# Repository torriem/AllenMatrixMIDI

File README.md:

# Allen MOS II Organ Keyboard Matrix to USB MIDI Adapter
This is a Teensy 4.1 sketch for connecting an Allen MOS II Organ's keyboards to a computer over USB MIDI.  It's designed to read the 11x18 combined keyboard matrix, and export them as a MIDI device suitable to connect to any virtual pipe organ.

## Operation
The keyboards all share a common set of read wires.  Each keyboard uses 11 read wires and the pedal board uses 7 of the 11.  Each keyboard has its own set of six signal wires.  To read the keyboards a microcontroller (the organ itself or a Teensy) raises each signal wire in turn to a high state and then reads the key pressed signals from the read wires.  This is done in a sequential cycle, reading many times per second. In this way a relatively few wires can read the entire keyboard quickly, and multiple keys can be pressed at once.

The MOS II Organ, at least our vintage, has its keyboard matrices wired in a peculiar way.  The first key has it's own output wire, and subsequent groups of six keys have their own output wire.  Diodes prevent back feeding. 

The input wires are done differently. There are six input wires per keyboard and each wire feeds the input of every sixth key, with the 61st key having input wire 1 into it.

This asymmetry between the input wires and the output wire groups means the mapping is a little strange.  See the end of this document for a chart.  You can also see the mapping in the ino file.

Here's a diagram of how an individual keyboard is wired.  Both keyboards are wired like this, but each has its own set of six input wires. The pedal board also has six input wires, but only uses seven output wires.  The OUT wires in the diagram are the eleven black wires going to the keyboard matrix board edge connector.

You cannot connect the Teensy to the keyboard at the same time the normal organ circuitry is connected.  A circuit board is needed to use relays to galvanically switch the keyboard between the stock organ and the Allen internal circuitry.

The sketch turns keyboard presses and releases into MIDI NOTE ON and NOTE OFF events, with a velocity of 127.  The first keyboard events are on channel 1, the second on channel 2, and the pedal board on channel 3.  If you want to change it, you can set it in the sketch.

## Black common wires
The 11 black read wires connect to Teensy pins 20-30.  Looking at the keyboard from the top, the left-most key is connected to its own black wire to pin 20.  Every group of 6 keys after that connects via diodes to a common black wire and those go in order to pins 21 and higher.

Looking at the 44-pin MOS Matrix board connector, the connections are:

| Teensy | MOS Matrix pin |
| ------ | -------------- |
| 20     | 11             |
| 21     | 13             |
| 22     | 9              |
| 23     | 5              |
| 24     | 7              |
| 25     | 3              |
| 26     | 1              |
| 27     | 8              |
| 28     | 10             |
| 29     | 12             |
| 30     | 14             |

## Keyboard 1 Read Wires
The top keyboard matrix is read by sending high signals down six wires, each wire connected to 11 keys.  These are connected left to right to Teensy to pins 2,3,4,5,6,7.  These wires can also be accessed via the 44-pin keyboard matrix edge connector on 22,23,26,25,24, and 21. On our organ these wires are white.

| Teensy | MOS Matrix pin |
| ------ | -------------- |
| 2      | 22             |
| 3      | 23             |
| 4      | 26             |
| 5      | 25             |
| 6      | 24             |
| 7      | 21             |

## Keyboard 2 Read Wires
The second keyboard matrix is also read by sending high signals through six wires that connect to Teensy's pins 8,9,10,11,12,and 13.  On our organ these are orange wires and are connected to the edge connector to pins 28, 29, 32, 31, 30, and 27.

| Teensy | MOS Matrix pin |
| ------ | -------------- |
| 8      | 28             |
| 9      | 29             |
| 10     | 32             |
| 11     | 31             |
| 12     | 30             |
| 13     | 27             |

## Pedal Board Read Wires
The pedal board is read by sending high signals to six wires that connect to Teensy pins 14, 15, 16, 17, 18, and 19.  These wires are blue on our organ and connect to pins 40, 41, 44, 43, 42, and 39 on the 44 pin matrix edge connector. Note that only the first seven of the black read wires are used on the pedal board

| Teensy | MOS Matrix pin |
| ------ | -------------- |
| 14     | 40             |
| 15     | 41             |
| 16     | 44             |
| 17     | 43             |
| 18     | 42             |
| 19     | 39             |

## Mapping of keyboard wires to key/note

| Key | Note | Input | Output | Combination |
|-----|------|-------|--------|-------------|
|  1  | C2   | IN1   | OUT1    | IN1-OUT1 |
|  2  | C#2  | IN2   | OUT2    | IN2-OUT2 |
|  3  | D2   | IN3   | OUT2    | IN3-OUT2 |
|  4  | D#2  | IN4   | OUT2    | IN4-OUT2 |
|  5  | E2   | IN5   | OUT2    | IN5-OUT2 |
|  6  | F2   | IN6   | OUT2    | IN6-OUT2 |
|  7  | F#2  | IN1   | OUT2    | IN1-OUT2 |
|  8  | G2   | IN2   | OUT3    | IN2-OUT3 |
|  9  | G#2  | IN3   | OUT3    | IN3-OUT3 |
| 10  | A2   | IN4   | OUT3    | IN4-OUT3 |
| 11  | A#2  | IN5   | OUT3    | IN5-OUT3 |
| 12  | B2   | IN6   | OUT3    | IN6-OUT3 |
| 13  | C3   | IN1   | OUT3    | IN1-OUT3 |
| 14  | C#3  | IN2   | OUT4    | IN2-OUT4 |
| 15  | D3   | IN3   | OUT4    | IN3-OUT4 |
| 16  | D#3  | IN4   | OUT4    | IN4-OUT4 |
| 17  | E3   | IN5   | OUT4    | IN5-OUT4 |
| 18  | F3   | IN6   | OUT4    | IN6-OUT4 |
| 19  | F#3  | IN1   | OUT4    | IN1-OUT4 |
| 20  | G3   | IN2   | OUT5    | IN2-OUT5 |
| 21  | G#3  | IN3   | OUT5    | IN3-OUT5 |
| 22  | A3   | IN4   | OUT5    | IN4-OUT5 |
| 23  | A#3  | IN5   | OUT5    | IN5-OUT5 |
| 24  | B3   | IN6   | OUT5    | IN6-OUT5 |
| 25  | C4   | IN1   | OUT5    | IN1-OUT5 |
| 26  | C#4  | IN2   | OUT6    | IN2-OUT6 |
| 27  | D4   | IN3   | OUT6    | IN3-OUT6 |
| 28  | D#4  | IN4   | OUT6    | IN4-OUT6 |
| 29  | E4   | IN5   | OUT6    | IN5-OUT6 |
| 30  | F4   | IN6   | OUT6    | IN6-OUT6 |
| 31  | F#4  | IN1   | OUT6    | IN1-OUT6 |
| 32  | G4   | IN2   | OUT7    | IN2-OUT7 |
| 33  | G#4  | IN3   | OUT7    | IN3-OUT7 |
| 34  | A4   | IN4   | OUT7    | IN4-OUT7 |
| 35  | A#4  | IN5   | OUT7    | IN5-OUT7 |
| 36  | B4   | IN6   | OUT7    | IN6-OUT7 |
| 37  | C5   | IN1   | OUT7    | IN1-OUT7 |
| 38  | C#5  | IN2   | OUT8    | IN2-OUT8 |
| 39  | D5   | IN3   | OUT8    | IN3-OUT8 |
| 40  | D#5  | IN4   | OUT8    | IN4-OUT8 |
| 41  | E5   | IN5   | OUT8    | IN5-OUT8 |
| 42  | F5   | IN6   | OUT8    | IN6-OUT8 |
| 43  | F#5  | IN1   | OUT8    | IN1-OUT8 |
| 44  | G5   | IN2   | OUT9    | IN2-OUT9 |
| 45  | G#5  | IN3   | OUT9    | IN3-OUT9 |
| 46  | A5   | IN4   | OUT9    | IN4-OUT9 |
| 47  | A#5  | IN5   | OUT9    | IN5-OUT9 |
| 48  | B5   | IN6   | OUT9    | IN6-OUT9 |
| 49  | C6   | IN1   | OUT9    | IN1-OUT9 |
| 50  | C#6  | IN2   | OUT10   | IN2-OUT10 |
| 51  | D6   | IN3   | OUT10   | IN3-OUT10 |
| 52  | D#6  | IN4   | OUT10   | IN4-OUT10 |
| 53  | E6   | IN5   | OUT10   | IN5-OUT10 |
| 54  | F6   | IN6   | OUT10   | IN6-OUT10 |
| 55  | F#6  | IN1   | OUT10   | IN1-OUT10 |
| 56  | G6   | IN2   | OUT11   | IN2-OUT11 |
| 57  | G#6  | IN3   | OUT11   | IN3-OUT11 |
| 58  | A6   | IN4   | OUT11   | IN4-OUT11 |
| 59  | A#6  | IN5   | OUT11   | IN5-OUT11 |
| 60  | B6   | IN6   | OUT11   | IN6-OUT11 |
| 61  | C7   | IN1   | OUT11   | IN1-OUT11 |

## Issues

Currently the Teensy occasionally reboots.  This could be do to unstable voltage provided by a USB hub.  Possibly dedicated a 5v power supply to the Teensy is needed (A trace on the Teensy 4.1 has to be cut to safely do this), or a powered hub, or plug the Teensy directly into the computer.

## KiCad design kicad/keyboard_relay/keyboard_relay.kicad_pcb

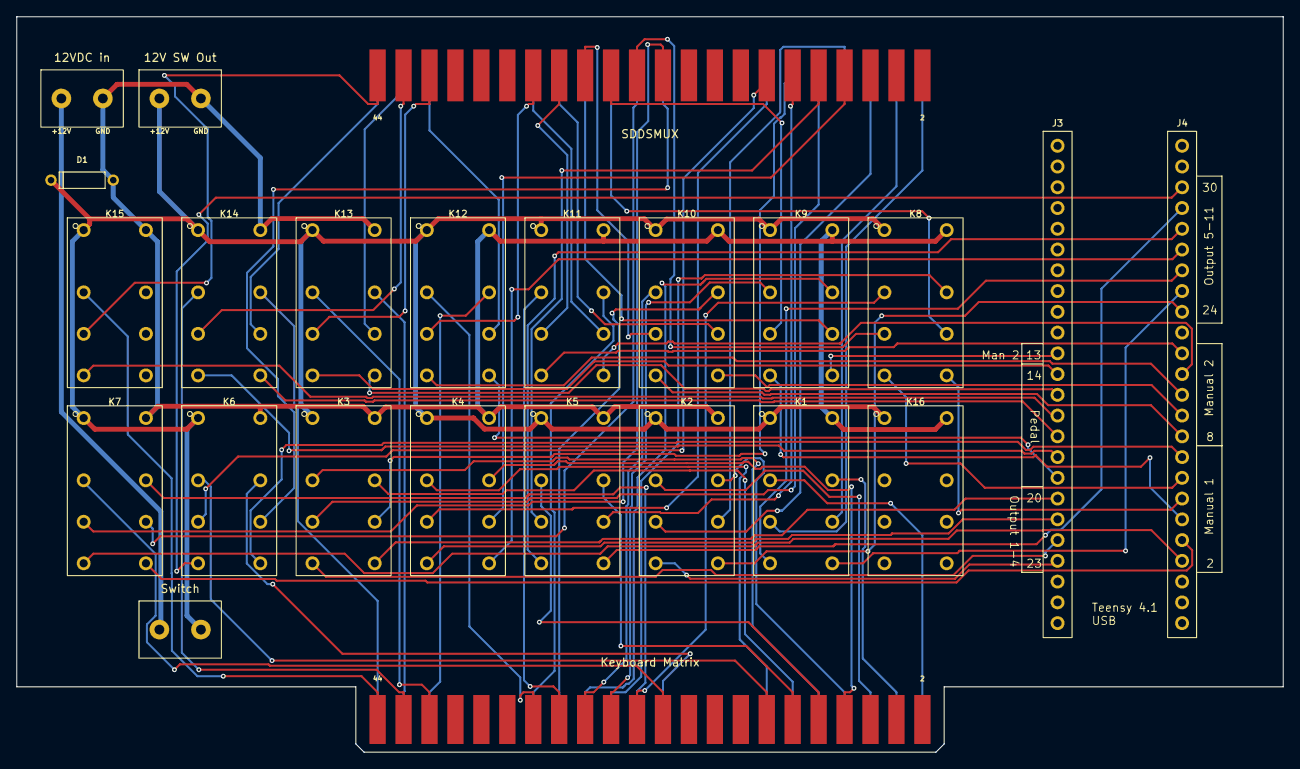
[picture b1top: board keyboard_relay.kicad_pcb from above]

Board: 2 copper layers, 155.0 x 90.0 mm, 24 parts (0 on the bottom side), 90 nets.

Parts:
12V SW Out, 12VDC in: 12V_Input; ScrewTerminal_2P
D1: 1N4148; D_DO35_Horizontal
J3, J4: Teensy_Header_24x1; PinHeader_24x1
K1, K2, K3, K4, K5, K6, K7, K8, K9, K10, K11, K12, K13, K14, K15, K16: HK19F-12V; Relay_HK19F_DIP8
Keyboard Matrix: Card_Edge_Male_44; CardEdge_Male_44
SDDSMUX: Card_Edge_Socket_44; CardEdge_Female_44
Switch: 12V_Input; ScrewTerminal_2P

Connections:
COIL_12V: 12VDC in.1, Switch.1
COIL_12V_SW: 12V SW Out.1, D1.K, K1.A1, K2.A1, K3.A1, K4.A1, K5.A1, K6.A1, K7.A1, K8.A1, K9.A1, K10.A1, K11.A1, K12.A1, K13.A1, K14.A1, K15.A1, K16.A1, Switch.2
COIL_GND: 12V SW Out.2, 12VDC in.2, D1.A, K1.A2, K2.A2, K3.A2, K4.A2, K5.A2, K6.A2, K7.A2, K8.A2, K9.A2, K10.A2, K11.A2, K12.A2, K13.A2, K14.A2, K15.A2, K16.A2
COMP_1: K1.12, SDDSMUX.1
COMP_3: K1.22, SDDSMUX.3
COMP_5: K2.12, SDDSMUX.5
COMP_7: K2.22, SDDSMUX.7
COMP_8: K4.22, SDDSMUX.8
COMP_9: K3.12, SDDSMUX.9
COMP_10: K5.12, SDDSMUX.10
COMP_11: K3.22, SDDSMUX.11
COMP_12: K5.22, SDDSMUX.12
COMP_13: K4.12, SDDSMUX.13
COMP_14: K6.12, SDDSMUX.14
COMP_21: K6.22, SDDSMUX.21
COMP_22: K7.12, SDDSMUX.22
COMP_23: K7.22, SDDSMUX.23
COMP_24: K8.12, SDDSMUX.24
COMP_25: K8.22, SDDSMUX.25
COMP_26: K9.12, SDDSMUX.26
COMP_27: K9.22, SDDSMUX.27
COMP_28: K10.12, SDDSMUX.28
COMP_29: K10.22, SDDSMUX.29
COMP_30: K11.12, SDDSMUX.30
COMP_31: K11.22, SDDSMUX.31
COMP_32: K12.12, SDDSMUX.32
COMP_39: K12.22, SDDSMUX.39
COMP_40: K13.12, SDDSMUX.40
COMP_41: K13.22, SDDSMUX.41
COMP_42: K14.12, SDDSMUX.42
COMP_43: K14.22, SDDSMUX.43
COMP_44: K15.12, SDDSMUX.44
KB_1: K1.11, Keyboard Matrix.1
KB_3: K1.21, Keyboard Matrix.3
KB_5: K2.11, Keyboard Matrix.5
KB_7: K2.21, Keyboard Matrix.7
KB_8: K4.21, Keyboard Matrix.8
KB_9: K3.11, Keyboard Matrix.9
KB_10: K5.11, Keyboard Matrix.10
KB_11: K3.21, Keyboard Matrix.11
KB_12: K5.21, Keyboard Matrix.12
KB_13: K4.11, Keyboard Matrix.13
KB_14: K6.11, Keyboard Matrix.14
KB_21: K6.21, Keyboard Matrix.21
KB_22: K7.11, Keyboard Matrix.22
KB_23: K7.21, Keyboard Matrix.23
KB_24: K8.11, Keyboard Matrix.24
KB_25: K8.21, Keyboard Matrix.25
KB_26: K9.11, Keyboard Matrix.26
KB_27: K9.21, Keyboard Matrix.27
KB_28: K10.11, Keyboard Matrix.28
KB_29: K10.21, Keyboard Matrix.29
KB_30: K11.11, Keyboard Matrix.30
KB_31: K11.21, Keyboard Matrix.31
KB_32: K12.11, Keyboard Matrix.32
KB_39: K12.21, Keyboard Matrix.39
KB_40: K13.11, Keyboard Matrix.40
KB_41: K13.21, Keyboard Matrix.41
KB_42: K14.11, Keyboard Matrix.42
KB_43: K14.21, Keyboard Matrix.43
KB_44: K15.11, Keyboard Matrix.44
TEEN_2: J4.21, K7.14
TEEN_3: J4.20, K7.24
TEEN_4: J4.19, K9.14
TEEN_5: J4.18, K8.24
TEEN_6: J4.17, K8.14
TEEN_7: J4.16, K6.24
TEEN_8: J4.15, K10.14
TEEN_9: J4.14, K10.24
TEEN_10: J4.13, K12.14
TEEN_11: J4.12, K11.24
TEEN_12: J4.11, K11.14
TEEN_13: J3.11, K9.24
TEEN_14: J3.12, K13.14
TEEN_15: J3.13, K13.24
TEEN_16: J3.14, K15.14
TEEN_17: J3.15, K14.24
TEEN_18: J3.16, K14.14
TEEN_19: J3.17, K12.24
TEEN_20: J3.18, K3.24
TEEN_21: J3.19, K4.14
TEEN_22: J3.20, K3.14
TEEN_23: J3.21, K2.14
TEEN_24: J4.9, K2.24
TEEN_25: J4.8, K1.24
TEEN_26: J4.7, K1.14
TEEN_27: J4.6, K4.24
TEEN_28: J4.5, K5.14
TEEN_29: J4.4, K5.24
TEEN_30: J4.3, K6.14

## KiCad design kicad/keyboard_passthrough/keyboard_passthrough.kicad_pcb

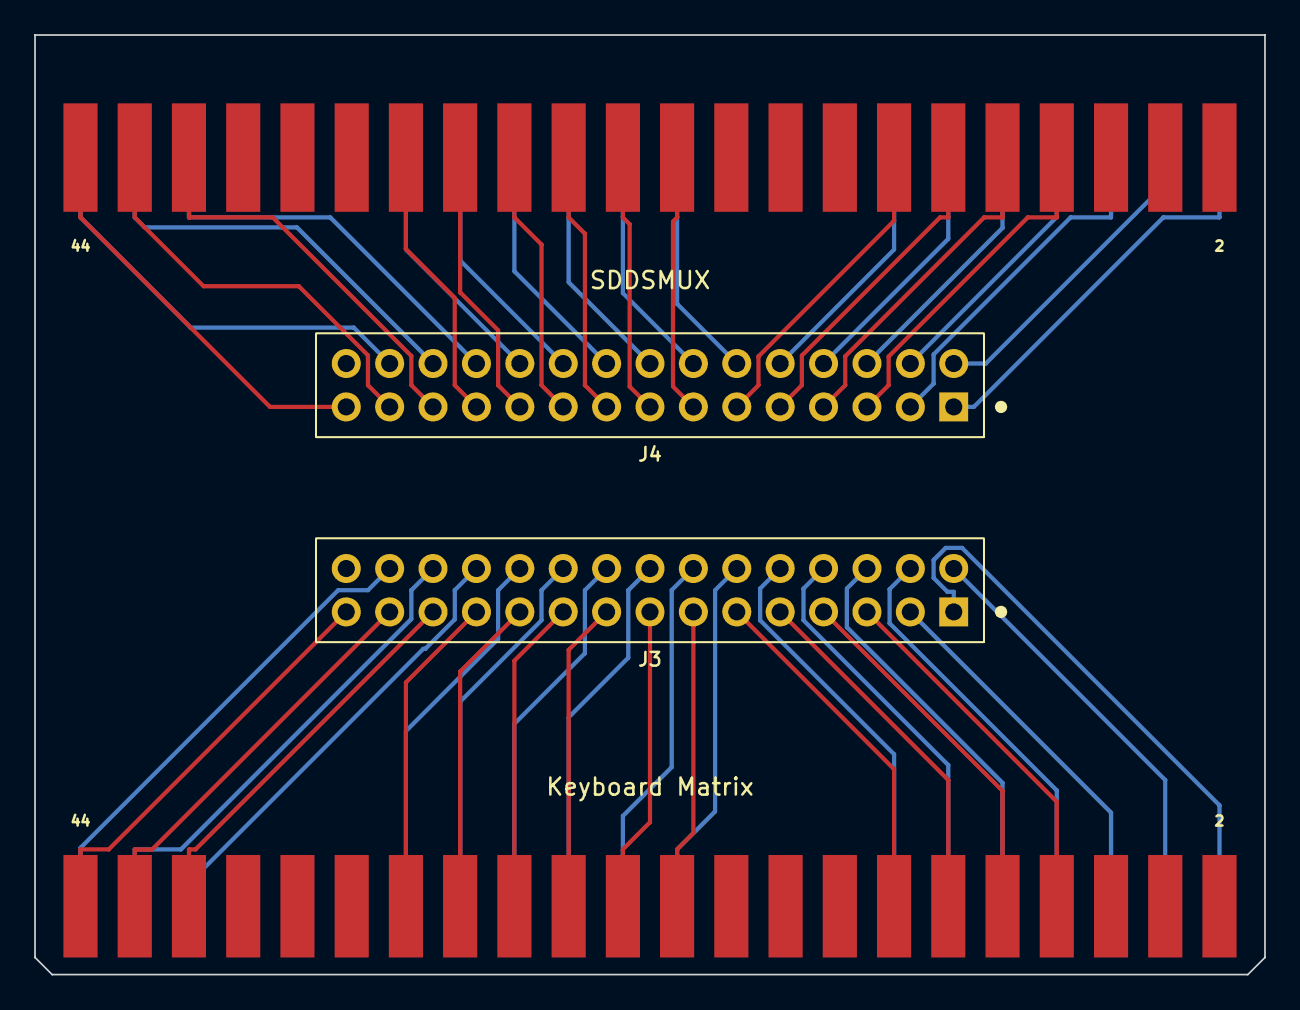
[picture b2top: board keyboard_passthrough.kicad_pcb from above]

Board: 2 copper layers, 72.0 x 55.0 mm, 4 parts (0 on the bottom side), 58 nets.

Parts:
J3: KB_Header; PinHeader_2x15
J4: COMP_Header; PinHeader_2x15
Keyboard Matrix: Card_Edge_Male_44; CardEdge_Male_44
SDDSMUX: Card_Edge_Socket_44; CardEdge_Female_44

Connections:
COMP_1: J4.1, SDDSMUX.1
COMP_3: J4.2, SDDSMUX.3
COMP_5: J4.3, SDDSMUX.5
COMP_7: J4.4, SDDSMUX.7
COMP_8: J4.5, SDDSMUX.8
COMP_9: J4.6, SDDSMUX.9
COMP_10: J4.7, SDDSMUX.10
COMP_11: J4.8, SDDSMUX.11
COMP_12: J4.9, SDDSMUX.12
COMP_13: J4.10, SDDSMUX.13
COMP_14: J4.11, SDDSMUX.14
COMP_21: J4.12, SDDSMUX.21
COMP_22: J4.13, SDDSMUX.22
COMP_23: J4.14, SDDSMUX.23
COMP_24: J4.15, SDDSMUX.24
COMP_25: J4.16, SDDSMUX.25
COMP_26: J4.17, SDDSMUX.26
COMP_27: J4.18, SDDSMUX.27
COMP_28: J4.19, SDDSMUX.28
COMP_29: J4.20, SDDSMUX.29
COMP_30: J4.21, SDDSMUX.30
COMP_31: J4.22, SDDSMUX.31
COMP_32: J4.23, SDDSMUX.32
COMP_39: J4.24, SDDSMUX.39
COMP_40: J4.25, SDDSMUX.40
COMP_41: J4.26, SDDSMUX.41
COMP_42: J4.27, SDDSMUX.42
COMP_43: J4.28, SDDSMUX.43
COMP_44: J4.29, SDDSMUX.44
KB_1: J3.1, Keyboard Matrix.1
KB_3: J3.2, Keyboard Matrix.3
KB_5: J3.3, Keyboard Matrix.5
KB_7: J3.4, Keyboard Matrix.7
KB_8: J3.5, Keyboard Matrix.8
KB_9: J3.6, Keyboard Matrix.9
KB_10: J3.7, Keyboard Matrix.10
KB_11: J3.8, Keyboard Matrix.11
KB_12: J3.9, Keyboard Matrix.12
KB_13: J3.10, Keyboard Matrix.13
KB_14: J3.11, Keyboard Matrix.14
KB_21: J3.12, Keyboard Matrix.21
KB_22: J3.13, Keyboard Matrix.22
KB_23: J3.14, Keyboard Matrix.23
KB_24: J3.15, Keyboard Matrix.24
KB_25: J3.16, Keyboard Matrix.25
KB_26: J3.17, Keyboard Matrix.26
KB_27: J3.18, Keyboard Matrix.27
KB_28: J3.19, Keyboard Matrix.28
KB_29: J3.20, Keyboard Matrix.29
KB_30: J3.21, Keyboard Matrix.30
KB_31: J3.22, Keyboard Matrix.31
KB_32: J3.23, Keyboard Matrix.32
KB_39: J3.24, Keyboard Matrix.39
KB_40: J3.25, Keyboard Matrix.40
KB_41: J3.26, Keyboard Matrix.41
KB_42: J3.27, Keyboard Matrix.42
KB_43: J3.28, Keyboard Matrix.43
KB_44: J3.29, Keyboard Matrix.44

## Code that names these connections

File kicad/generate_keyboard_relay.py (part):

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    # 12V screw terminal (left side)
    # 12V screw terminal above top row of relays
    # 12V screw terminal (+12V and GND)
    footprints.append(screw_terminal_fp("+12V", 8.0, power_y - 10.0, "COIL_12V", "COIL_GND", label1="+12V", label2="GND"))
    # Switch jumper: connects unswitched 12V to switched 12V via external switch
    footprints.append(screw_terminal_fp("Switch", 20.0, BOARD_H - 15.0, "COIL_12V", "COIL_12V_SW"))
    # Switched power output jumper (next to +12V input)
    footprints.append(screw_terminal_fp("12V_SW", 20.0, power_y - 10.0, "COIL_12V_SW", "COIL_GND", label1="+12V", label2="GND"))

    fp_str = "\n".join(footprints)
    outline = board_outline()
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
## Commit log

2026-02-12 inital commit.
2026-02-13 MIDI over USB working, all three channels working.
2026-02-13 Added readme and license
2026-02-13 refactor: use named constants for MIDI channels
2026-02-13 renamed ino
2026-02-13 updated readme.
2026-02-14 Added delay between setting signal wires high, to deal with diode recovery time. Also increased settling time after setting a signal wire high before the read wires are read.
2026-02-15 Altered the mapping of wires to notes to reflect the peculiarities of how our MOS II organ is wired. Added a keyboard wiring diagram, and some ancilliary python scripts to generate the diagram, and t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
2026-02-15 To be clear the six wires per keyboard aren't read wires, they are signal wires.
2026-02-18 Claude designed circuit board via python script.
2026-02-19 Renamed kicad python script.
2026-02-19 Added a pass-through breakout board that puts the wires into headers that can either be connected together or taken to another board. Also added keep out zones to pcbs to keep tracese from routing ne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
2026-02-19 Added generated kicad files with routed traces using freerouting.
2026-03-22 Improve MIDI stability and rename USB device to Allen Organ MIDI.
    Move debouncer array to heap to reduce stack usage. Add USB-ready
    checks before sending MIDI to prevent blocking on a dead connection.
    Flush note-off burst in batches during setup to avoid send buffer
    overflow. Send all-notes-off on startup for clean state. Fix
    uninitialized channel variable in scanMatrix.
2026-03-23 latest kicad schematic and board layout. Note the pcb needs routing, possibly using freerouting plugin.
